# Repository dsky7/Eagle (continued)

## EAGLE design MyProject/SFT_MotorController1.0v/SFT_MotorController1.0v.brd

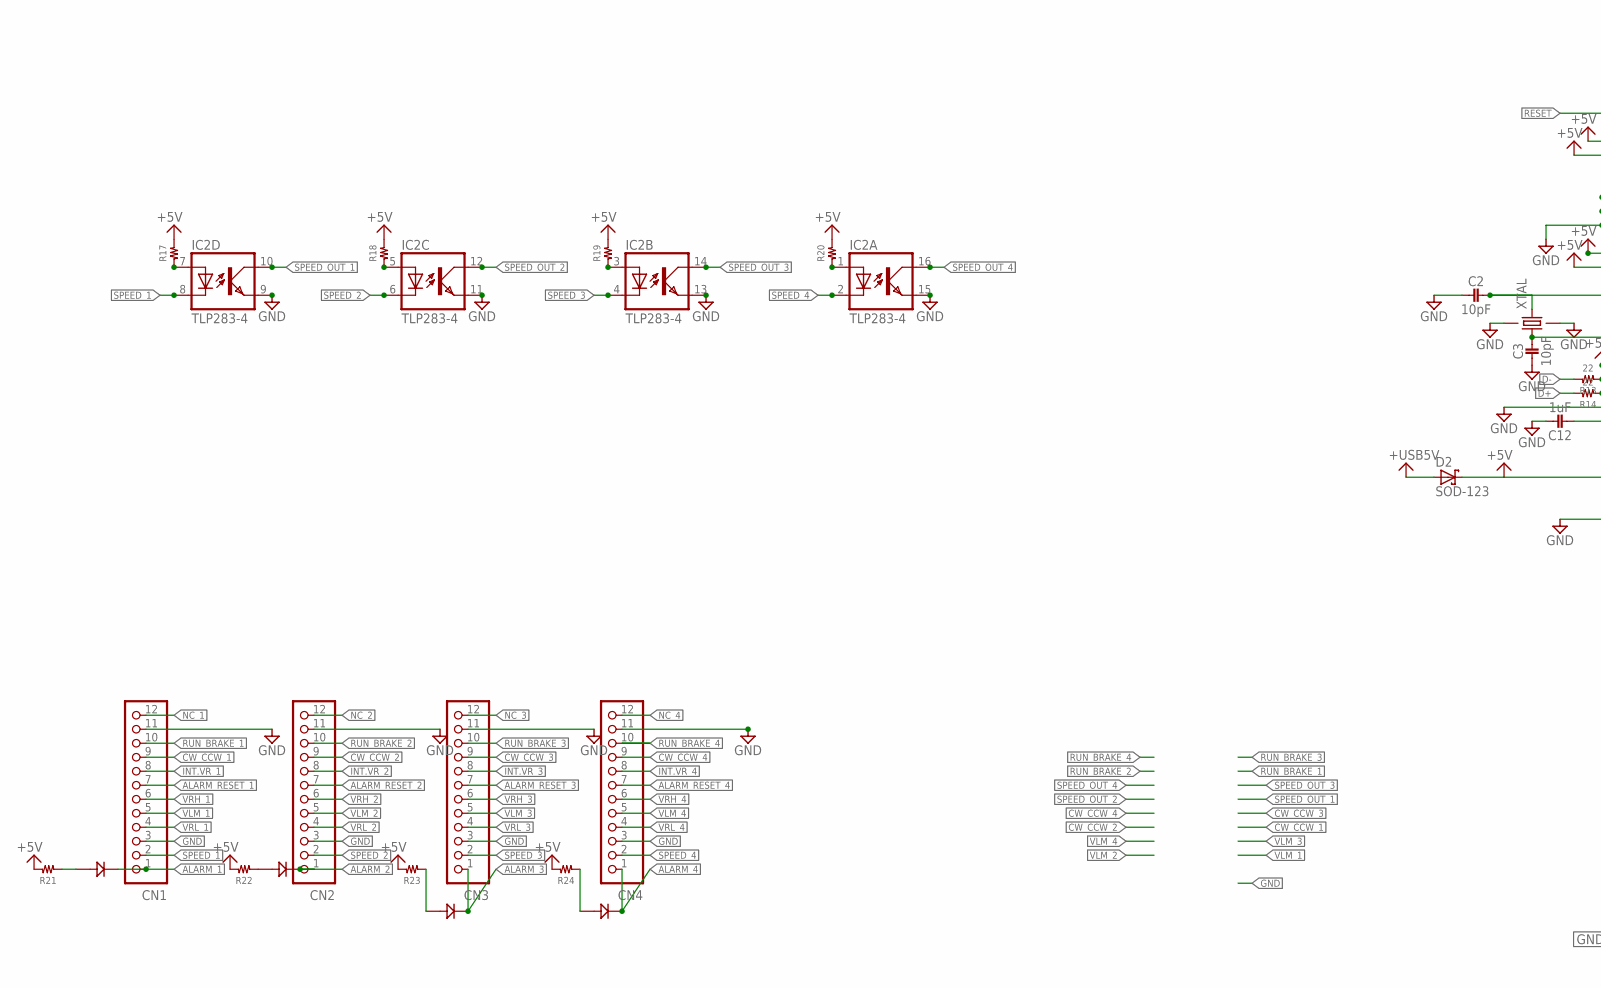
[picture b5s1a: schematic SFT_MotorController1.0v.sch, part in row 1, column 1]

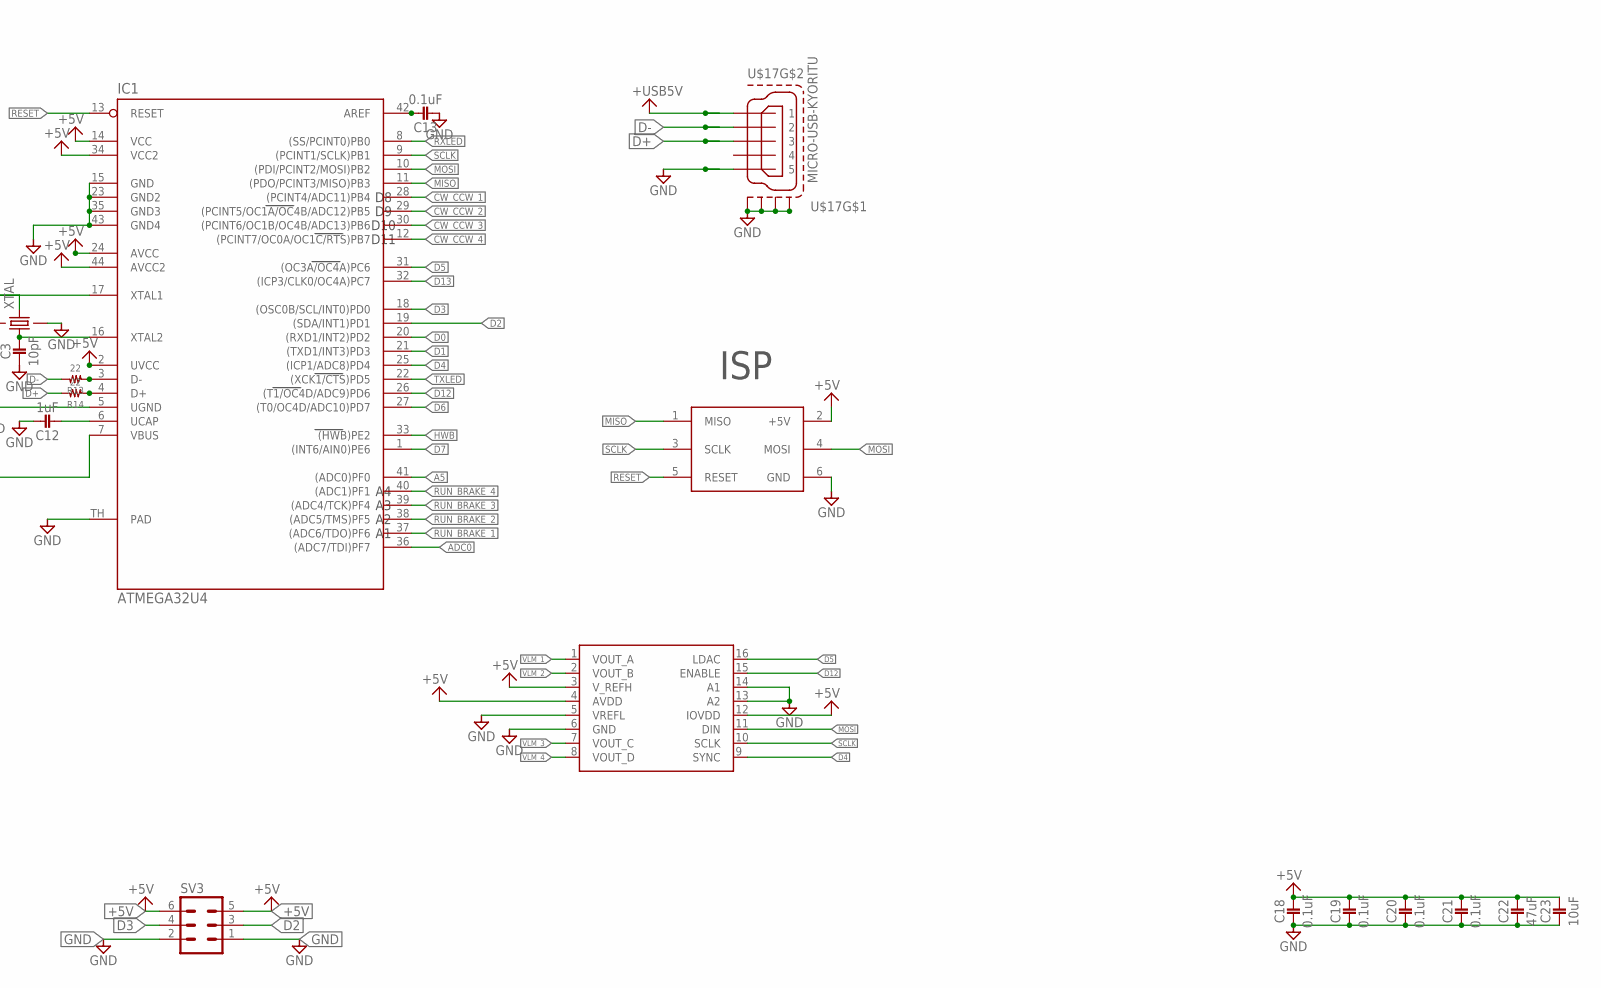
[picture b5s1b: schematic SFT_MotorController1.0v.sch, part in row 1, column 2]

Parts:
C2, C3: 10pF; 1005
C12: 1uF; 1005
C13, C18, C19, C20, C21: 0.1uF; 1005
C22: 47uF; 1608
C23: 10uF; 1608
CN1, CN2, CN3, CN4: B12B-XASK-1
D2: SOD-123; SOD_123
IC1: ATMEGA32U4; QFN-44-7X7
IC2: TLP283-4; MINI-FLAT-16
IC3: DAC7564; TSSOP16
R13, R14: 22; 1005
R17, R18, R19, R20, R21, R22, R23, R24: RESISTOR__SMD; 1608
SV3: ML6
U$8: ICSP
U$17: MICRO-USB-KYORITU; ZX62R-B-5P
U$36, U$37, U$38, U$39: 3MMLED; 3MM
XTAL: FA-238

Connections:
+5V: C18.1, C19.1, C20.1, C21.1, C22.P$1 (1), C23.P$1 (1), D2.C, IC1.2 (UVCC), IC1.7 (VBUS), IC1.14 (VCC), IC1.24 (AVCC), IC1.34 (VCC2), IC1.44 (AVCC2), IC3.3 (V_REFH), IC3.4 (AVDD), IC3.12 (IOVDD), R17.2, R18.2, R19.2, R20.2, R21.2, R22.2, R23.2, R24.2, SV3.5, SV3.6, U$8.2 (+5V)
+USB5V: D2.A, U$17.5 (1)
A5: IC1.41 ((ADC0)PF0)
ADC0: IC1.36 ((ADC7/TDI)PF7)
ALARM_1: CN1.1, U$37.K
ALARM_2: CN2.1, U$38.K
ALARM_3: CN3.1, U$36.K
ALARM_4: CN4.1, U$39.K
ALARM_RESET_1: CN1.7
ALARM_RESET_2: CN2.7
ALARM_RESET_3: CN3.7
ALARM_RESET_4: CN4.7
CW_CCW_1: CN1.9, IC1.28 ((PCINT4/ADC11)PB4)
CW_CCW_2: CN2.9, IC1.29 ((PCINT5/OC1A/OC4B/ADC12)PB5)
CW_CCW_3: CN3.9, IC1.30 ((PCINT6/OC1B/OC4B/ADC13)PB6)
CW_CCW_4: CN4.9, IC1.12 ((PCINT7/OC0A/OC1C/RTS)PB7)
D0: IC1.20 ((RXD1/INT2)PD2)
D1: IC1.21 ((TXD1/INT3)PD3)
D2: IC1.19 ((SDA/INT1)PD1), SV3.3
D3: IC1.18 ((OSC0B/SCL/INT0)PD0), SV3.4
D4: IC1.25 ((ICP1/ADC8)PD4), IC3.9 (SYNC)
D5: IC1.31 ((OC3A/OC4A)PC6), IC3.16 (LDAC)
D6: IC1.27 ((T0/OC4D/ADC10)PD7)
D7: IC1.1 ((INT6/AIN0)PE6)
D12: IC1.26 ((T1/OC4D/ADC9)PD6), IC3.15 (ENABLE)
D13: IC1.32 ((ICP3/CLK0/OC4A)PC7)
D+: R14.2, U$17.3
D-: R13.2, U$17.4 (2)
GND: C2.2, C3.2, C12.1, C13.2, C18.2, C19.2, C20.2, C21.2, C22.P$2 (2), C23.P$2 (2), CN1.3, CN1.11, CN2.3, CN2.11, CN3.3, CN3.11, CN4.3, CN4.11, IC1.5 (UGND), IC1.15 (GND), IC1.23 (GND2), IC1.35 (GND3), IC1.43 (GND4), IC1.TH (PAD), IC2.9 (EMIT), IC2.11 (EMIT), IC2.13 (EMIT), IC2.15 (EMIT), IC3.5 (VREFL), IC3.6 (GND), IC3.13 (A2), IC3.14 (A1), SV3.1, SV3.2, U$8.6 (GND), U$17.1 (5), U$17.M1 (S1), U$17.M2 (S2), U$17.M3 (S3), U$17.M4 (S4), XTAL.2, XTAL.4
HWB: IC1.33 ((HWB)PE2)
INT.VR_1: CN1.8
INT.VR_2: CN2.8
INT.VR_3: CN3.8
INT.VR_4: CN4.8
MISO: IC1.11 ((PDO/PCINT3/MISO)PB3), U$8.1 (MISO)
MOSI: IC1.10 ((PDI/PCINT2/MOSI)PB2), IC3.11 (DIN), U$8.4 (MOSI)
unnamed: IC1.3 (D-), R13.1
unnamed: IC1.4 (D+), R14.1
unnamed: C3.1, IC1.16 (XTAL2), XTAL.1
unnamed: R22.1, U$38.A
unnamed: IC2.3 (A), R19.1
unnamed: IC2.5 (A), R18.1
unnamed: IC2.7 (A), R17.1
unnamed: IC2.1 (A), R20.1
unnamed: C13.1, IC1.42 (AREF)
unnamed: C2.1, IC1.17 (XTAL1), XTAL.3
unnamed: R21.1, U$37.A
unnamed: R23.1, U$36.A
unnamed: R24.1, U$39.A
unnamed: C12.2, IC1.6 (UCAP)
NC_1: CN1.12
NC_2: CN2.12
NC_3: CN3.12
NC_4: CN4.12
RESET: IC1.13 (RESET), U$8.5 (RESET)
RUN_BRAKE_1: CN1.10, IC1.37 ((ADC6/TDO)PF6)
RUN_BRAKE_2: CN2.10, IC1.38 ((ADC5/TMS)PF5)
RUN_BRAKE_3: CN3.10, IC1.39 ((ADC4/TCK)PF4)
RUN_BRAKE_4: CN4.10, IC1.40 ((ADC1)PF1)
RXLED: IC1.8 ((SS/PCINT0)PB0)
SCLK: IC1.9 ((PCINT1/SCLK)PB1), IC3.10 (SCLK), U$8.3 (SCLK)
SPEED_1: CN1.2, IC2.8 (C)
SPEED_2: CN2.2, IC2.6 (C)
SPEED_3: CN3.2, IC2.4 (C)
SPEED_4: CN4.2, IC2.2 (C)
SPEED_OUT_1: IC2.10 (COL)
SPEED_OUT_2: IC2.12 (COL)
SPEED_OUT_3: IC2.14 (COL)
SPEED_OUT_4: IC2.16 (COL)
TXLED: IC1.22 ((XCK1/CTS)PD5)
VLM_1: CN1.5, IC3.1 (VOUT_A)
VLM_2: CN2.5, IC3.2 (VOUT_B)
VLM_3: CN3.5, IC3.7 (VOUT_C)
VLM_4: CN4.5, IC3.8 (VOUT_D)
VRH_1: CN1.6
VRH_2: CN2.6
VRH_3: CN3.6
VRH_4: CN4.6
VRL_1: CN1.4
VRL_2: CN2.4
VRL_3: CN3.4
VRL_4: CN4.4

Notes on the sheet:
ISP
D10
D11

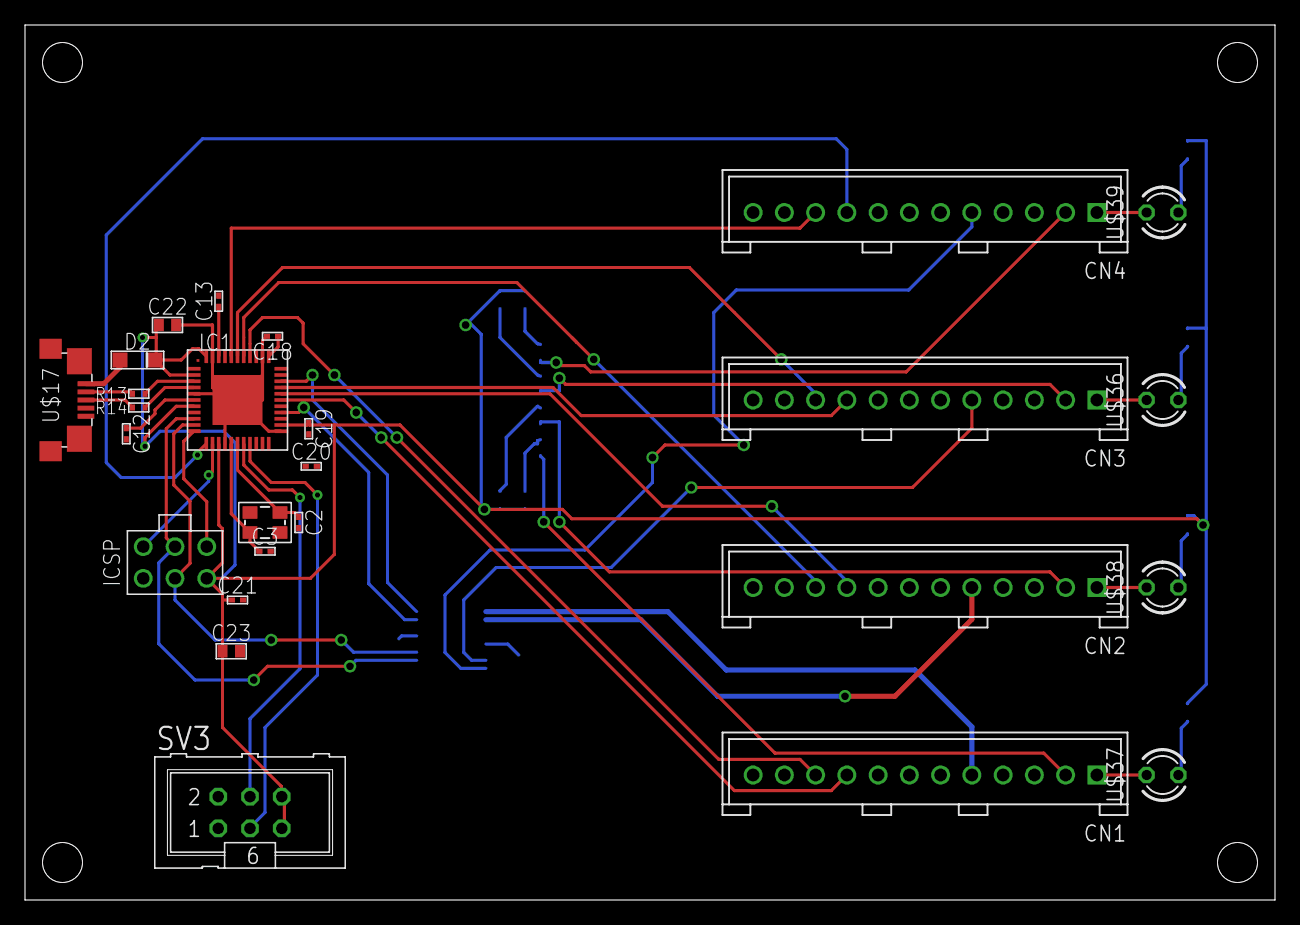
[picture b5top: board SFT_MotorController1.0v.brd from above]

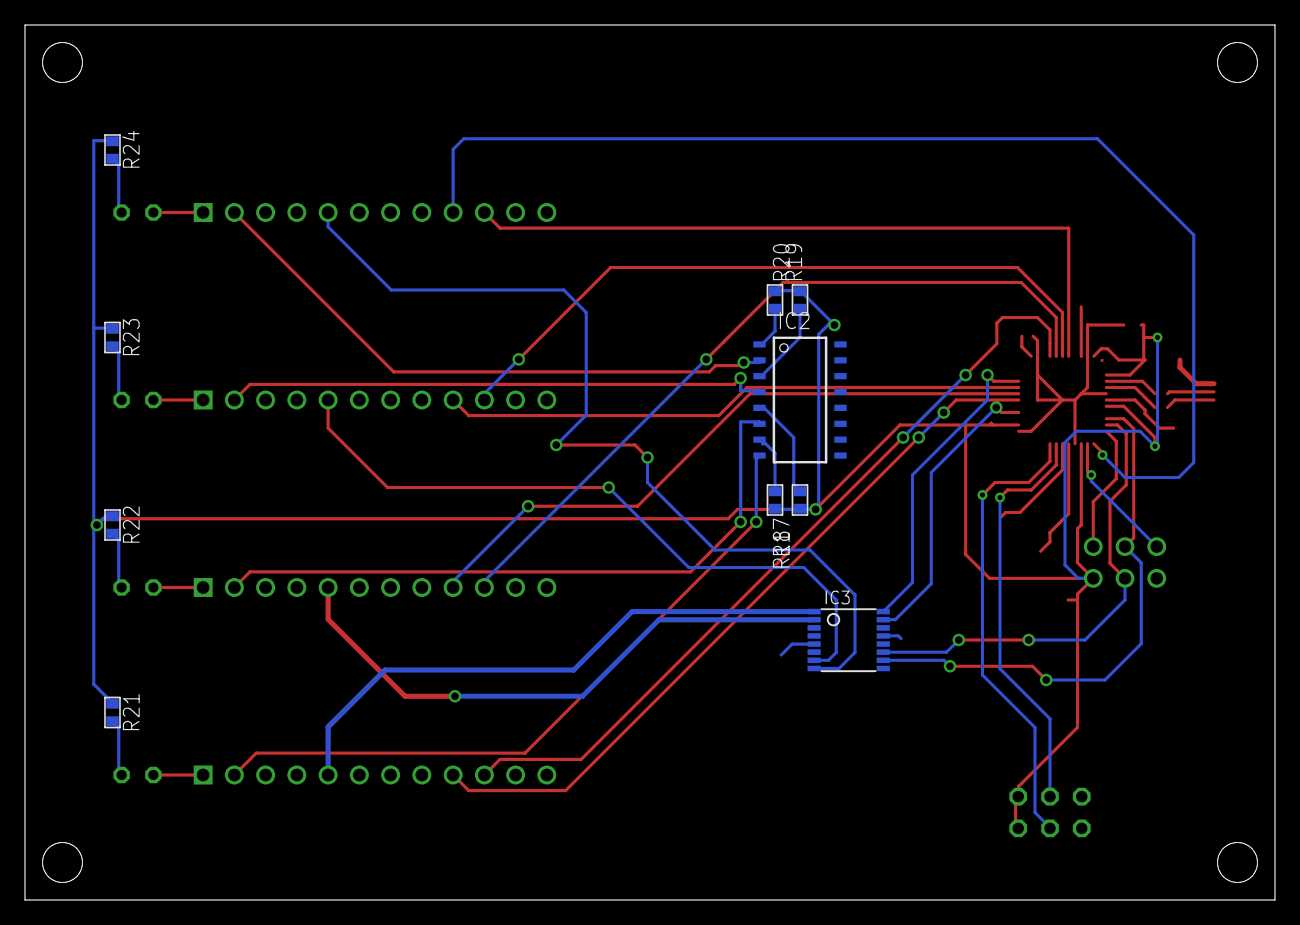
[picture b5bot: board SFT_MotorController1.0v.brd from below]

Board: 2 copper layers, 100.0 x 70.0 mm, 36 parts (10 on the bottom side), 48 nets.

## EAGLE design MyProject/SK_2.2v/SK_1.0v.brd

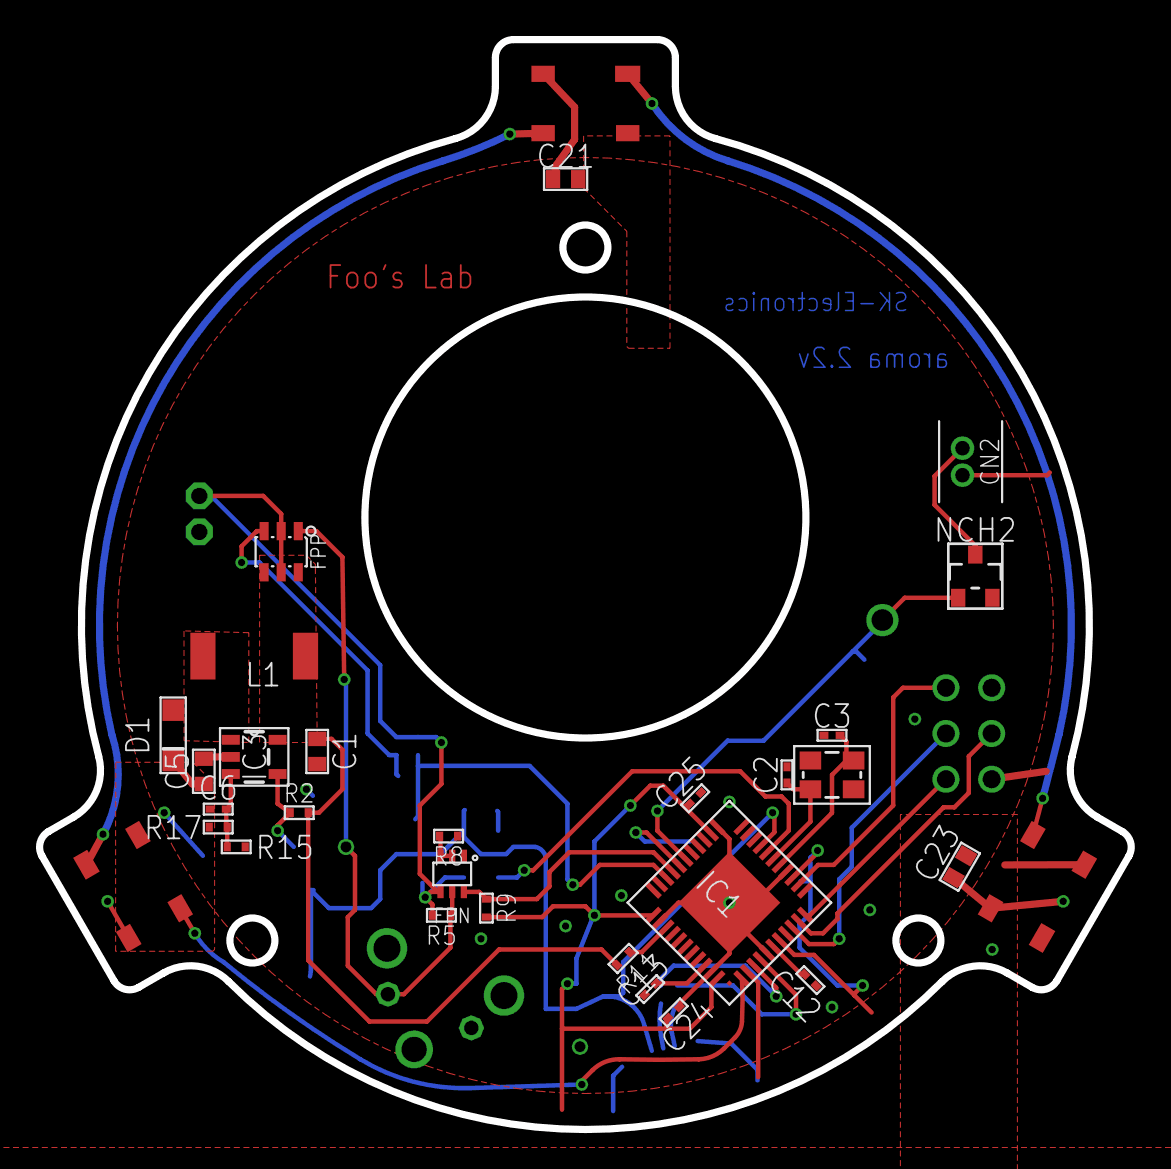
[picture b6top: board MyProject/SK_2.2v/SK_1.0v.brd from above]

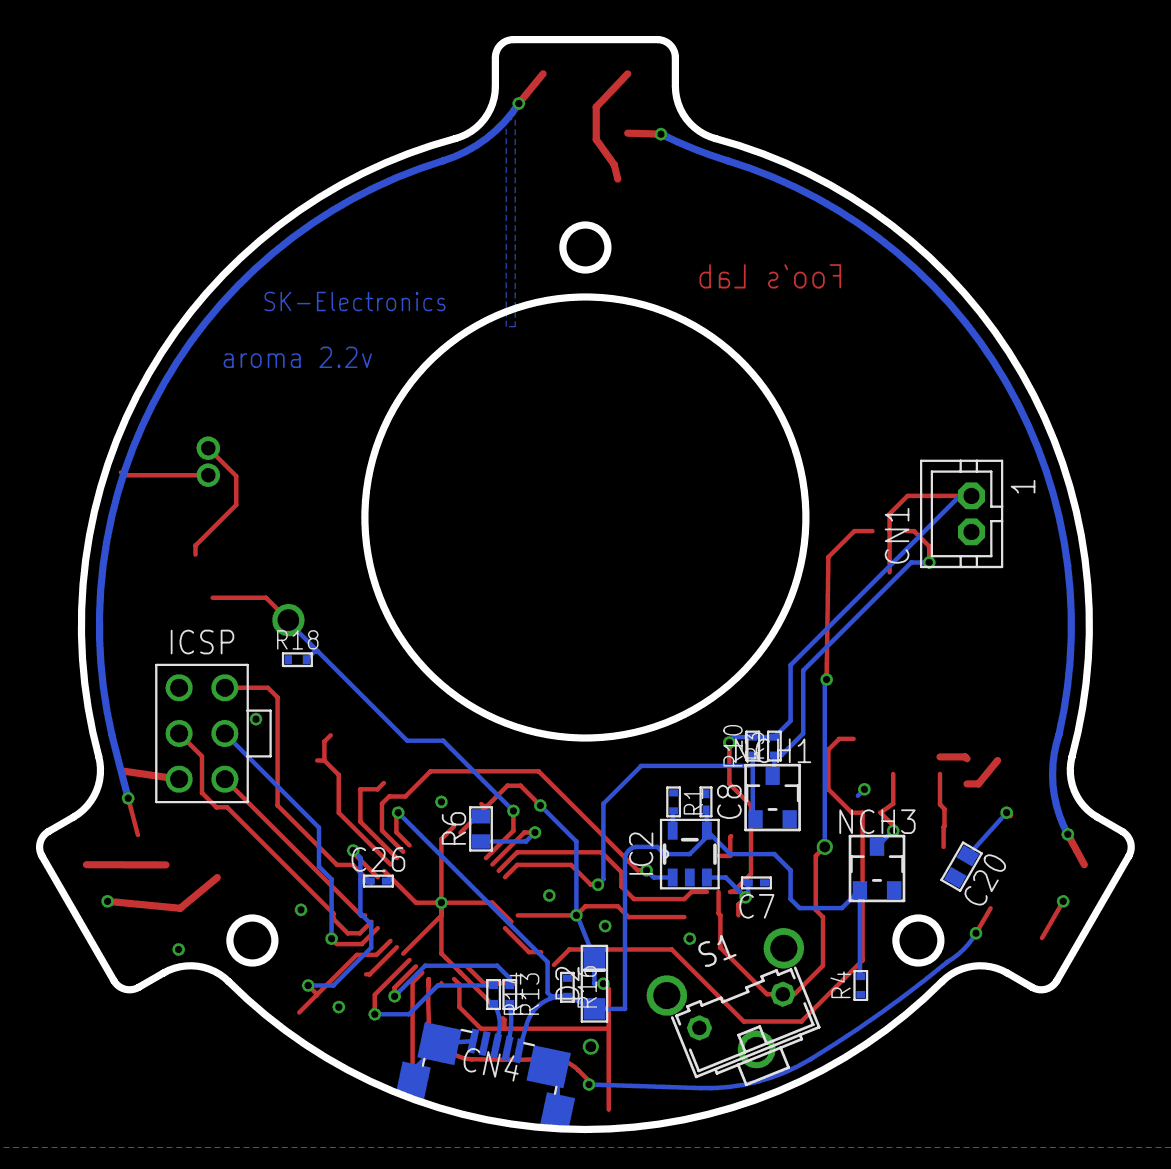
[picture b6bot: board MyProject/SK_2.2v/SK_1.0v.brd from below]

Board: 2 copper layers, 60.6 x 60.5 mm, 51 parts (21 on the bottom side), 34 nets.

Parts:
C1, C5: 22uF; 1608
C2, C3: 22pF; 1005
C6: 1nF; 1005
C7, C8: 4.7uF; 1005
C12: 1uF; 1005
C13, C24, C25, C26: 0.1uF; 1005
C20, C21, C23: 0.1uF; 1608
CN1: JST-PH2-CENTER
CN2: B2B-ZR-CENTER
CN4: usb; ZX62R-B-5P
D1, D2: SOD-123; SOD_123
FPN: SI1553CDL; SOT363
FPP: FDC6506P; SOT23-6
IC1: ATMEGA32U4; QFN-44-7X7
IC2: MCP73831; SOT23-5L
IC3: LM2735; SOT23-5L
L1: 22uH; TOKO
LED1, LED2, LED3: NEO_FLAT
NCH1, NCH2, NCH3: Nch; SOT23
R1: 2K; 1005
R2, R4, R10: 100K; 1005
R3, R5, R8, R9, R15, R16, R18: 10K; 1005
R6: 1608
R11: 1K; 1005
R13, R14: 22; 1005
R17: 30K; 1005
S1: B3F-31XX
U$3: ICSP
U$8: FA-238

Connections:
+3.7V: C1.P$1, FPP.4, FPP.6, IC3.5, L1.1, R2.2, R11.2
+5V: C5.P$1, C6.1, C20.P$1, C21.P$1, C23.P$1, C24.1, C25.1, C26.1, CN2.1, D1.C, D2.C, IC1.2, IC1.7, IC1.14, IC1.24, IC1.34, IC1.44, LED1.1, LED2.1, LED3.1, R9.2, R17.2, U$3.2
+USB5V: C8.1, CN4.1, D2.A, IC1.19, IC2.4, NCH3.1, R4.2, R16.2
ADC0: IC1.36, R11.1
D5: IC1.31, NCH1.1, R10.1
D7: IC1.1, LED3.4
D8: IC1.28, NCH2.1, R18.2
D9: IC1.29, R6.2
D10: FPN.6, IC1.30, R9.1
D+: CN4.3, R14.2
D-: CN4.2, R13.2
DL: D1.A, IC3.1, L1.2
FB: C6.2, IC3.3, R15.2, R17.1
GND: C1.P$2, C2.2, C3.2, C5.P$2, C7.2, C8.2, C12.1, C13.2, C20.P$2, C21.P$2, C23.P$2, C24.2, C25.2, C26.2, CN1.2, CN4.5, CN4.M1, CN4.M2, CN4.M3, CN4.M4, FPN.1, IC1.5, IC1.15, IC1.23, IC1.35, IC1.43, IC1.TH, IC2.2, IC3.2, LED1.3, LED2.3, LED3.3, NCH1.2, NCH2.2, NCH3.2, R1.1, R4.1, R8.1, R15.1, R16.1, R18.1, S1.1, S1.3, S1.4, S1.5, U$3.6, U$8.2, U$8.4
MISO: IC1.11, U$3.1
MOSI: IC1.10, U$3.4
unnamed: CN2.2, NCH2.3
unnamed: IC2.5, R1.2
unnamed: IC3.4, NCH3.3, R2.1
unnamed: FPP.3, NCH1.3, R3.1
unnamed: C3.1, IC1.16, U$8.1
unnamed: IC1.3, R13.1
unnamed: C13.1, IC1.42
unnamed: C2.1, IC1.17, U$8.3
unnamed: IC1.4, R14.1
unnamed: C12.2, IC1.6
RESET: IC1.13, U$3.5
SCLK: IC1.9, U$3.3
SIG: FPN.2, FPN.3, R8.2
SIG1: LED2.4, LED3.2
SIG2: LED1.4, LED2.2
STAT: IC1.18, IC2.1
SWSIG: FPN.5, FPP.1, R5.1, S1.2
V2: C7.1, CN1.1, FPN.4, FPP.2, FPP.5, IC2.3, R3.2, R5.2, R10.2

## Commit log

2015-04-19 commit1
2015-04-19 eagle file 追加
2015-04-19 add sft bord
2015-04-20 月曜バイト行く前の更新
2015-04-20 月曜バイト終了
2015-04-22 TETUYA KOUSIN
2015-04-23 yokuwakarannga toriaezu
2015-04-27 baitomae
2015-04-27 kannsei kana
2015-04-27 BAITO SYUURYOU
2015-04-29 syukujitu syuuryou
2015-04-30 kyuukei reset
2015-04-30 tetuya
2015-05-11 test2
2015-05-11 baito owatta
2015-05-14 toukyougo
2015-05-14 tetuya ake
2015-05-25 ArduinoMicroShield1.0v kannsei
2015-05-25 sinnya
2015-06-22 puti tenjikai
2015-08-20 Foo's Lab
2016-01-03 test
2016-01-03 saisin
2016-01-03 testtest
2016-01-08 baito mae hatu
2016-01-08 baito owari hatu
2016-01-12 baito mae2
2016-05-23 hisashiburi
